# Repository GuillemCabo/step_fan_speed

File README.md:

# step\_fan\_speed

## Description 
Simple PCB to control computer fan speed with a atinny88

The board runs out of the fan 12V, step down to 3.3V with an LDO.

It provides a PWM header in and PWM out. The MCU is able to intercept the
signal of the tachometer and generated a new PWM signal.

## Usage 
The uart is accesible through a two pin headeris. External FTDI bridge is required
if you want to connect it to the computer.

The board is programmed  thorugh ISP with a Tag-connect cable or UART if a
bootloader if it has been previously programmed.

## IO
* 3 DIP switches
* 1 Push button
* 2 LEDs 
* NTC sensor.
* I2C port (As SMD pads)
* PMW in
* PWM out
* UART

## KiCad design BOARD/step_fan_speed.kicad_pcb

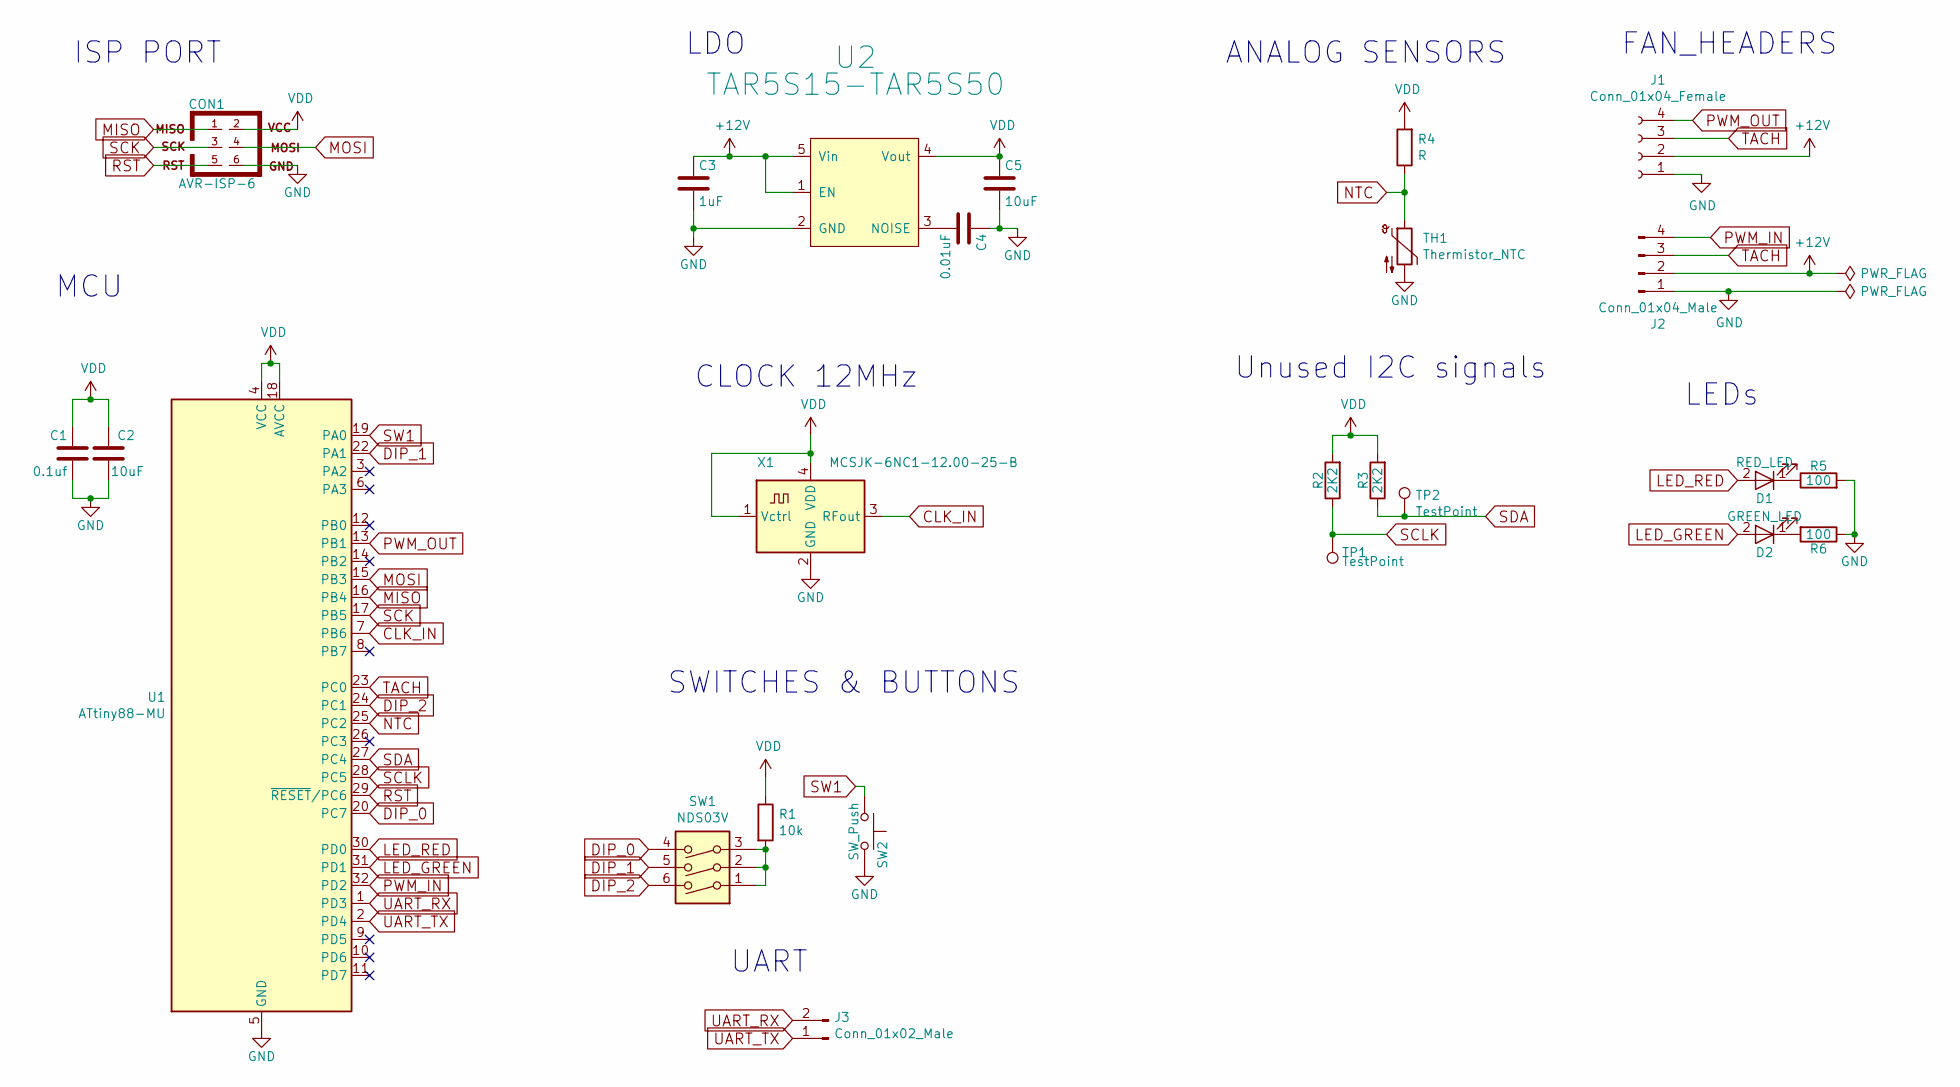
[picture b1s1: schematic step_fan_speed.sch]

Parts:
C1: 0.1uf; C_0603_1608Metric; MPN C0603C104J5RACTU; FARNELL # 2409037
C2: 10uF; C_0805_2012Metric; MPN C0805X106K9RACTU; FARNELL # 2776900
C3: 1uF; C_0603_1608Metric; MPN C0603C105K9RACTU; FARNELL # 1865556
C4: 0.01uF; C_0603_1608Metric; MPN C0603C105K9RACTU; FARNELL # 1865556
C5: 10uF; C_0805_2012Metric; MPN C0603C105K9RACTU; FARNELL # 1865556
CON1: AVR-ISP-6; Tag-Connect_TC2030-IDC-NL_2x03_P1.27mm_Vertical; MPN NONE; FARNELL # NONE
D1: RED_LED; KPA-1606; MPN KPA-1606SURCK; FARNELL # 2290358
D2: GREEN_LED; KPA-1606; MPN KPA-1606CGCK; FARNELL # 2290360
J1: Conn_01x04_Female; PinSocket_1x04_P2.54mm_Horizontal
J2: Conn_01x04_Male; PinHeader_1x04_P2.54mm_Horizontal
J3: Conn_01x02_Male; PinHeader_1x02_P2.54mm_Horizontal
R1: 10k; R_0603_1608Metric; MPN CRCW1206100RFKEA
R2, R3: 2K2; R_0603_1608Metric; MPN MC0063W060354K7; FARNELL # 9332154
R4: R; R_0603_1608Metric
R5, R6: 100; R_0603_1608Metric; FARNELL # 1469752
SW1: NDS03V; SW_DIP_SPSTx03_Slide_9.78x9.8mm_W7.62mm_P2.54mm; MPN NDS03V
SW2: SW_Push; SW_Push_1P1T_NO_CK_KSC7xxJ; MPN EVQPUK02K; FARNELL # 2079467
TH1: Thermistor_NTC; R_Axial_DIN0204_L3.6mm_D1.6mm_P2.54mm_Vertical
TP1, TP2: TestPoint; TestPoint_Pad_1.5x1.5mm
U1: ATtiny88-MU; QFN-32-1EP_5x5mm_P0.5mm_EP3.1x3.1mm; MPN ATTINY88-MU; FARNELL # 1748549
U2: TAR5S15-TAR5S50; SOT-23-5_HandSoldering
X1: MCSJK-6NC1-12.00-25-B; Oscillator_SMD_EuroQuartz_XO91-4Pin_7.0x5.0mm_HandSoldering

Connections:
+12V: C3.1, J1.2, J2.2, U2.1 (EN), U2.5 (Vin)
CLK_IN: U1.7 (PB6), X1.3 (RFout)
DIP_0: SW1.4, U1.20 (PC7)
DIP_1: SW1.5, U1.22 (PA1)
DIP_2: SW1.6, U1.24 (PC1)
GND: C1.2, C2.2, C3.2, C4.1, C5.2, CON1.6, J1.1, J2.1, R5.2, R6.1, SW2.2, TH1.2, U1.5 (GND), U1.21 (GND), U1.33 (GND), U2.2 (GND), X1.2 (GND)
LED_GREEN: D2.2 (A), U1.31 (PD1)
LED_RED: D1.2 (A), U1.30 (PD0)
MISO: CON1.1, U1.16 (PB4)
MOSI: CON1.4, U1.15 (PB3)
NTC: R4.1, TH1.1, U1.25 (PC2)
unnamed: C4.2, U2.3 (NOISE)
unnamed: D1.1 (K), R5.1
unnamed: D2.1 (K), R6.2
unnamed: R1.2, SW1.1, SW1.2, SW1.3
PWM_IN: J2.4, U1.32 (PD2)
PWM_OUT: J1.4, U1.13 (PB1)
RST: CON1.5, U1.29 (~RESET~/PC6)
SCK: CON1.3, U1.17 (PB5)
SCLK: R2.1, TP1.1, U1.28 (PC5)
SDA: R3.1, TP2.1, U1.27 (PC4)
SW1: SW2.1, U1.19 (PA0)
TACH: J1.3, J2.3, U1.23 (PC0)
UART_RX: J3.2, U1.1 (PD3)
UART_TX: J3.1, U1.2 (PD4)
VDD: C1.1, C2.1, C5.1, CON1.2, R1.1, R2.2, R3.2, R4.2, U1.4 (VCC), U1.18 (AVCC), U2.4 (Vout), X1.1 (Vctrl), X1.4 (VDD)

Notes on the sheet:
LDO
ISP PORT
FAN_HEADERS
Unused I2C signals
LEDs
SWITCHES & BUTTONS
ANALOG SENSORS
MCU
CLOCK 12MHz
UART

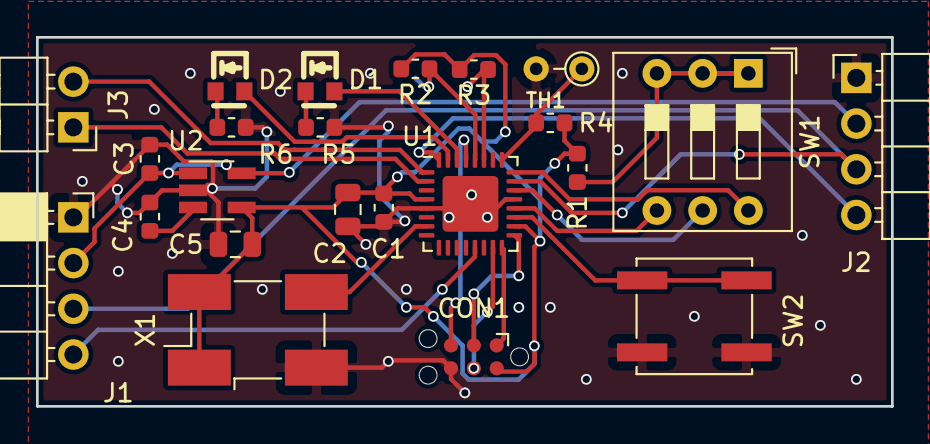
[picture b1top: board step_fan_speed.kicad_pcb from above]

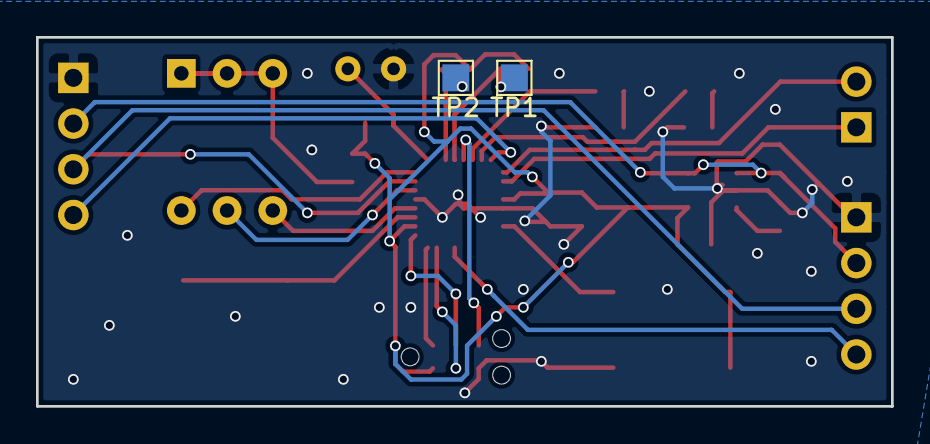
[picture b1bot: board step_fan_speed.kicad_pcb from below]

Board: 2 copper layers, 47.5 x 20.5 mm, 25 parts (2 on the bottom side), 26 nets.

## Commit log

2020-05-18 Layout done
